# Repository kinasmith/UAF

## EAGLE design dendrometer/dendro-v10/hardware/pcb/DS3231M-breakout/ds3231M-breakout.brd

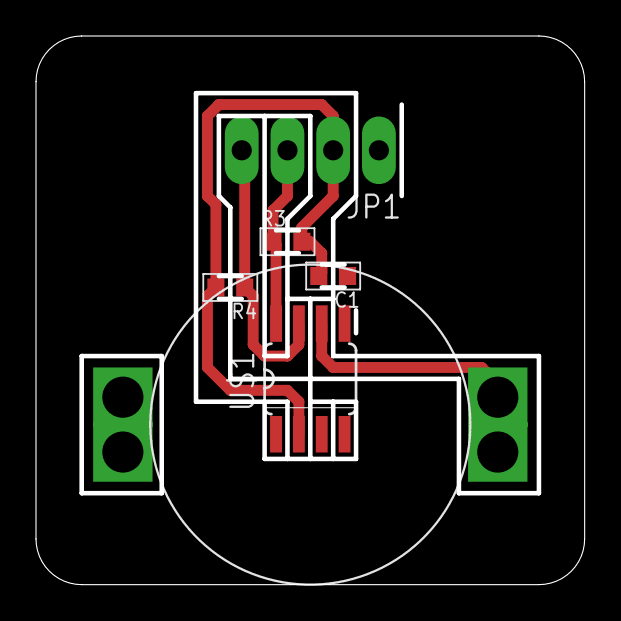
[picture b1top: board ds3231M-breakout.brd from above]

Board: 2 copper layers, 30.5 x 30.5 mm, 6 parts (0 on the bottom side), 5 nets.

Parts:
C1: 0.1uf; C0603-N
JP1: 1X04_LONGPADS
R3, R4: 10k; R0603-N
U$1: DS3231M; SO08
U$2: LINX_2032BAT_HLDER

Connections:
GND: C1.1, JP1.1, U$1.5, U$2.P$1
unnamed: U$1.6, U$2.BAT_POS$1, U$2.BAT_POS$2, U$2.BAT_POS$3, U$2.BAT_POS$4
SCL: JP1.3, R3.1, U$1.8
SDA: JP1.4, R4.1, U$1.7
VCC: C1.2, JP1.2, R3.2, R4.2, U$1.2

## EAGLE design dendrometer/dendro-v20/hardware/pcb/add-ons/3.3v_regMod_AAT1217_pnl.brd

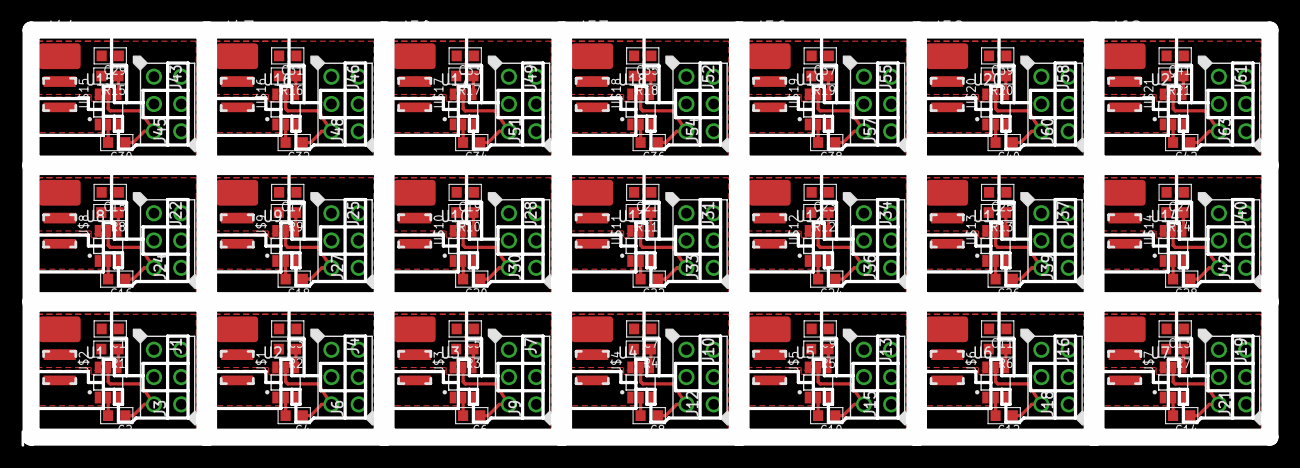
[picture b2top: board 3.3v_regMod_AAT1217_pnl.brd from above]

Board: 2 copper layers, 116.0 x 38.6 mm, 168 parts (0 on the bottom side), 105 nets.

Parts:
C1, C2, C3, C4, C5, C6, C7, C8, C9, C10, C11, C12, C13, C14, C15, C16, C17, C18, C19, C20, C21, C22, C23, C24, C25, C26, C27, C28, C29, C30, C31, C32, C33, C34, C35, C36, C37, C38, C39, C40, C41, C42: C0603-N
J1, J3, J4, J6, J7, J9, J10, J12, J13, J15, J16, J18, J19, J21, J22, J24, J25, J27, J28, J30, J31, J33, J34, J36, J37, J39, J40, J42, J43, J45, J46, J48, J49, J51, J52, J54, J55, J57, J58, J60, J61, J63: MF-CON-2.54mm-01x03; PTH_2.54MM_01X03
J2, J5, J8, J11, J14, J17, J20, J23, J26, J29, J32, J35, J38, J41, J44, J47, J50, J53, J56, J59, J62: CON_01X01LUX; 1X01_LUXEON-PAD
R1, R2, R3, R4, R5, R6, R7, R8, R9, R10, R11, R12, R13, R14, R15, R16, R17, R18, R19, R20, R21: 1M; R0603-N
U1, U2, U3, U4, U5, U6, U7, U8, U9, U10, U11, U12, U13, U14, U15, U16, U17, U18, U19, U20, U21: AAT1217-SOT23-6; SOT23-6
U$1, U$2, U$3, U$4, U$5, U$6, U$7, U$8, U$9, U$10, U$11, U$12, U$13, U$14, U$15, U$16, U$17, U$18, U$19, U$20, U$21: L3030

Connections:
3V1: C4.1, J4.P$3, U2.5
3V2: C6.1, J7.P$3, U3.5
3V3: C2.1, J1.P$3, U1.5
3V4: C8.1, J10.P$3, U4.5
3V5: C10.1, J13.P$3, U5.5
3V6: C12.1, J16.P$3, U6.5
3V7: C14.1, J19.P$3, U7.5
3V8: C16.1, J22.P$3, U8.5
3V9: C18.1, J25.P$3, U9.5
3V10: C20.1, J28.P$3, U10.5
3V11: C22.1, J31.P$3, U11.5
3V12: C24.1, J34.P$3, U12.5
3V13: C26.1, J37.P$3, U13.5
3V14: C28.1, J40.P$3, U14.5
3V15: C30.1, J43.P$3, U15.5
3V16: C32.1, J46.P$3, U16.5
3V17: C34.1, J49.P$3, U17.5
3V18: C36.1, J52.P$3, U18.5
3V19: C38.1, J55.P$3, U19.5
3V20: C40.1, J58.P$3, U20.5
3V21: C42.1, J61.P$3, U21.5
GND: C1.1, C2.2, J1.P$1, U1.2
GND1: C3.1, C4.2, J4.P$1, U2.2
GND2: C5.1, C6.2, J7.P$1, U3.2
GND3: C7.1, C8.2, J10.P$1, U4.2
GND4: C9.1, C10.2, J13.P$1, U5.2
GND5: C11.1, C12.2, J16.P$1, U6.2
GND6: C13.1, C14.2, J19.P$1, U7.2
GND7: C15.1, C16.2, J22.P$1, U8.2
GND8: C17.1, C18.2, J25.P$1, U9.2
GND9: C19.1, C20.2, J28.P$1, U10.2
GND10: C21.1, C22.2, J31.P$1, U11.2
GND11: C23.1, C24.2, J34.P$1, U12.2
GND12: C25.1, C26.2, J37.P$1, U13.2
GND13: C27.1, C28.2, J40.P$1, U14.2
GND14: C29.1, C30.2, J43.P$1, U15.2
GND15: C31.1, C32.2, J46.P$1, U16.2
GND16: C33.1, C34.2, J49.P$1, U17.2
GND17: C35.1, C36.2, J52.P$1, U18.2
GND18: C37.1, C38.2, J55.P$1, U19.2
GND19: C39.1, C40.2, J58.P$1, U20.2
GND20: C41.1, C42.2, J61.P$1, U21.2
unnamed: U1.1, U$2.P$2
unnamed: U2.1, U$1.P$2
unnamed: R1.1, U1.4
unnamed: R2.1, U2.4
unnamed: U3.1, U$3.P$2
unnamed: R3.1, U3.4
unnamed: U4.1, U$4.P$2
unnamed: R4.1, U4.4
unnamed: U5.1, U$5.P$2
unnamed: R5.1, U5.4
unnamed: U6.1, U$6.P$2
unnamed: R6.1, U6.4
unnamed: U7.1, U$7.P$2
unnamed: R7.1, U7.4
unnamed: U8.1, U$8.P$2
unnamed: R8.1, U8.4
unnamed: U9.1, U$9.P$2
unnamed: R9.1, U9.4
unnamed: U10.1, U$10.P$2
unnamed: R10.1, U10.4
unnamed: U11.1, U$11.P$2
unnamed: R11.1, U11.4
unnamed: U12.1, U$12.P$2
unnamed: R12.1, U12.4
unnamed: U13.1, U$13.P$2
unnamed: R13.1, U13.4
unnamed: U14.1, U$14.P$2
unnamed: R14.1, U14.4
unnamed: U15.1, U$15.P$2
unnamed: R15.1, U15.4
unnamed: U16.1, U$16.P$2
unnamed: R16.1, U16.4
unnamed: U17.1, U$17.P$2
unnamed: R17.1, U17.4
unnamed: U18.1, U$18.P$2
unnamed: R18.1, U18.4
unnamed: U19.1, U$19.P$2
unnamed: R19.1, U19.4
unnamed: U20.1, U$20.P$2
unnamed: R20.1, U20.4
unnamed: U21.1, U$21.P$2
unnamed: R21.1, U21.4
V_BAT: C1.2, J2.P$1, R1.2, U1.6, U$2.P$1
V_BAT1: C3.2, J5.P$1, R2.2, U2.6, U$1.P$1
V_BAT2: C5.2, J8.P$1, R3.2, U3.6, U$3.P$1
V_BAT3: C7.2, J11.P$1, R4.2, U4.6, U$4.P$1
V_BAT4: C9.2, J14.P$1, R5.2, U5.6, U$5.P$1
V_BAT5: C11.2, J17.P$1, R6.2, U6.6, U$6.P$1
V_BAT6: C13.2, J20.P$1, R7.2, U7.6, U$7.P$1
V_BAT7: C15.2, J23.P$1, R8.2, U8.6, U$8.P$1
V_BAT8: C17.2, J26.P$1, R9.2, U9.6, U$9.P$1
V_BAT9: C19.2, J29.P$1, R10.2, U10.6, U$10.P$1
V_BAT10: C21.2, J32.P$1, R11.2, U11.6, U$11.P$1
V_BAT11: C23.2, J35.P$1, R12.2, U12.6, U$12.P$1
V_BAT12: C25.2, J38.P$1, R13.2, U13.6, U$13.P$1
V_BAT13: C27.2, J41.P$1, R14.2, U14.6, U$14.P$1
V_BAT14: C29.2, J44.P$1, R15.2, U15.6, U$15.P$1
V_BAT15: C31.2, J47.P$1, R16.2, U16.6, U$16.P$1
V_BAT16: C33.2, J50.P$1, R17.2, U17.6, U$17.P$1
V_BAT17: C35.2, J53.P$1, R18.2, U18.6, U$18.P$1
V_BAT18: C37.2, J56.P$1, R19.2, U19.6, U$19.P$1
V_BAT19: C39.2, J59.P$1, R20.2, U20.6, U$20.P$1
V_BAT20: C41.2, J62.P$1, R21.2, U21.6, U$21.P$1

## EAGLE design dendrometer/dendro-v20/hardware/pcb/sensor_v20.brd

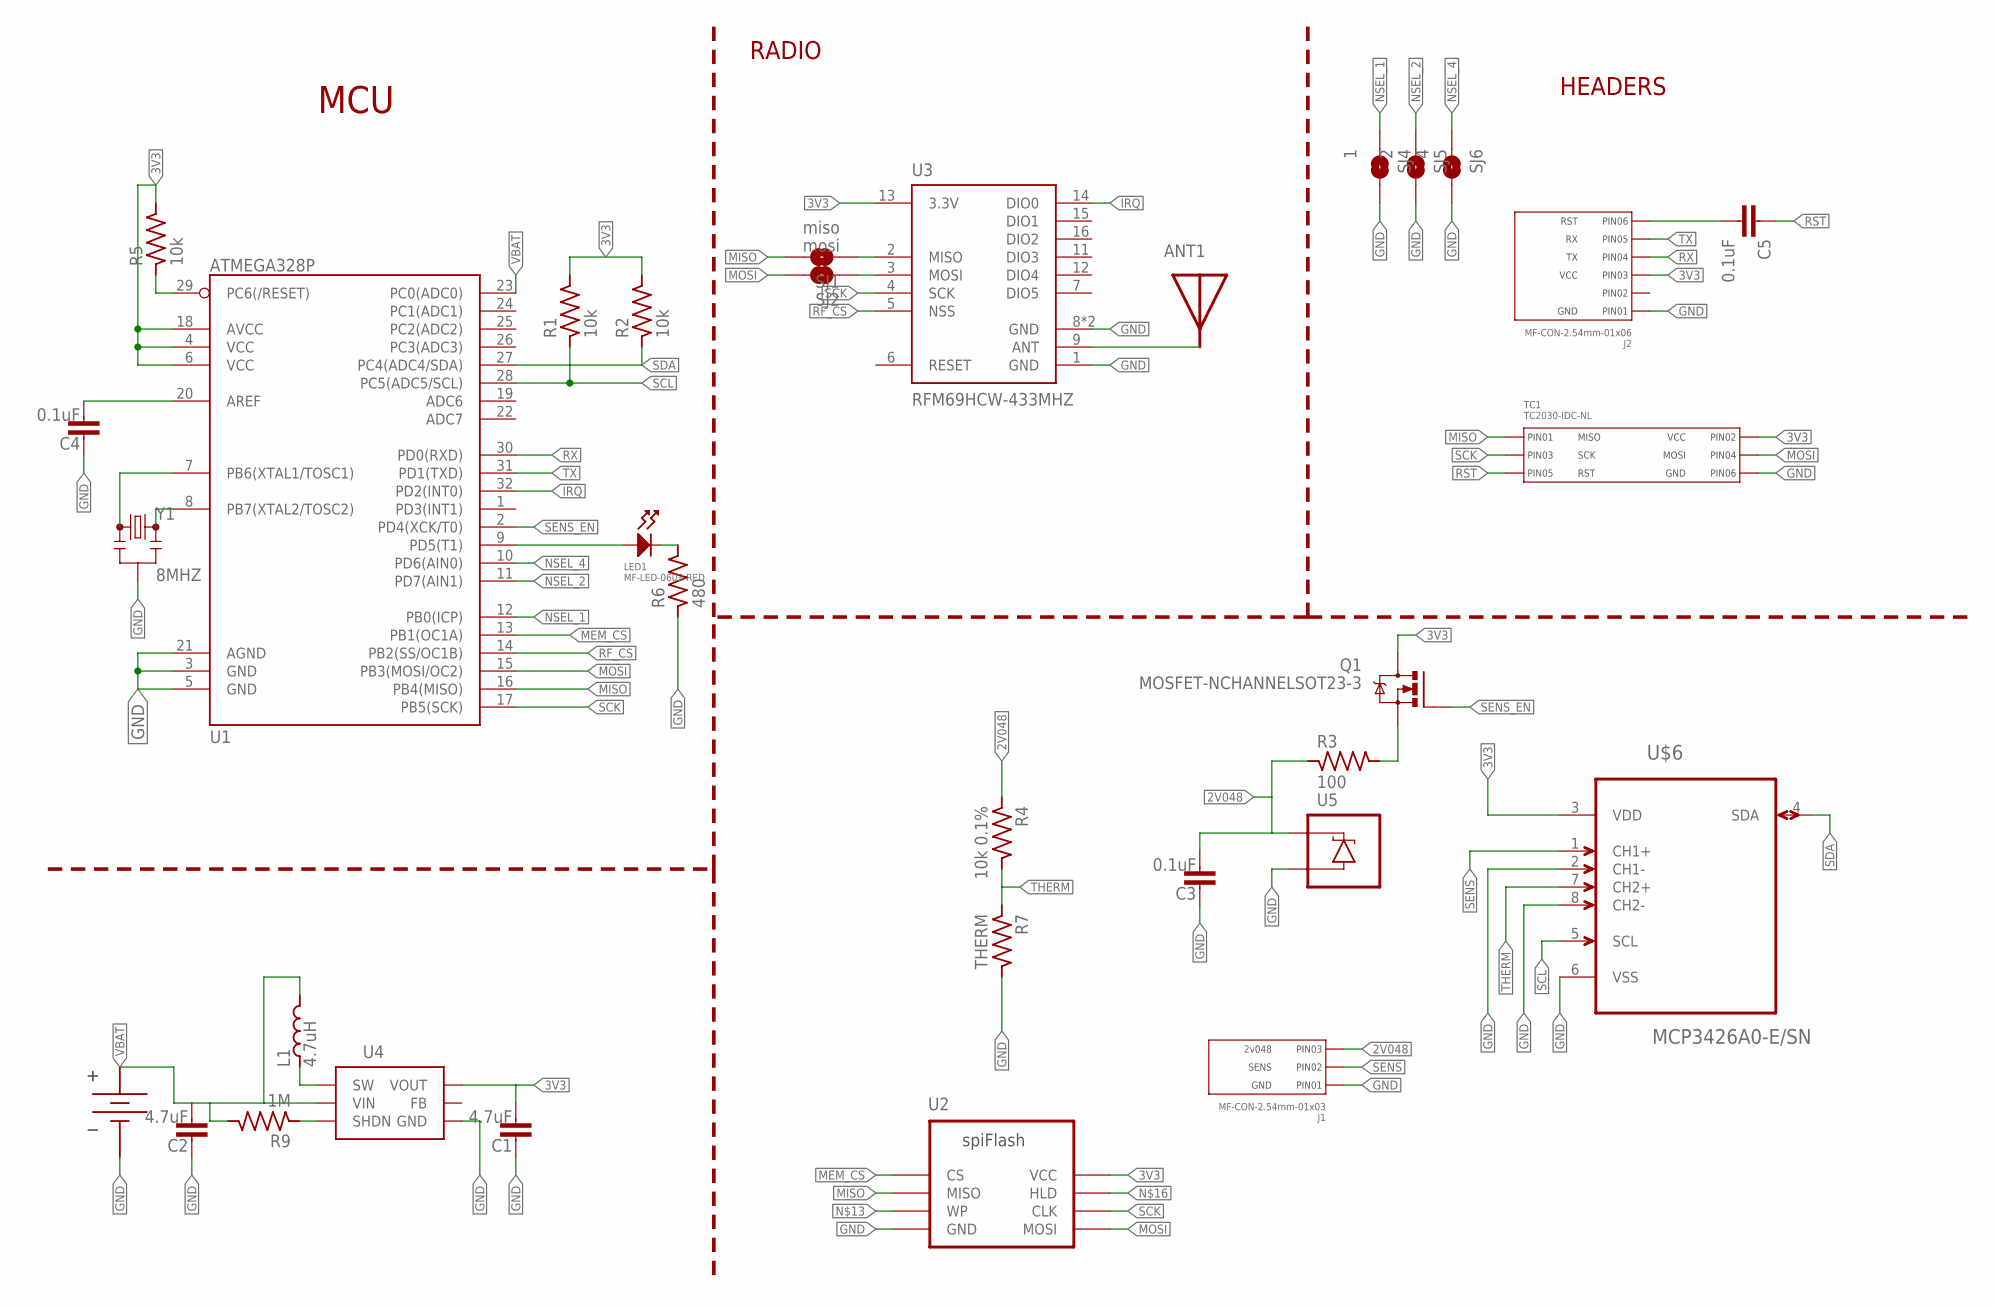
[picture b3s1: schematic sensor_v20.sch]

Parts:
ANT1: ANTENNA-433_CHIP; ANT_433_CHIP
C1, C2: 4.7uF; C0603-N
C3, C4, C5: 0.1uF; C0603-N
J1: MF-CON-2.54mm-01x03; PTH_2.54MM_01X03; PARTNO 0022053031
J2: MF-CON-2.54mm-01x06; PTH_2.54MM_01X06
L1: 4.7uH; L3030
LED1: MF-LED-0603-RED; LED0603
Q1: MOSFET-NCHANNELSOT23-3; SOT23-3
R1, R2, R5: 10k; R0603-N
R3: 100; R0603-N
R4: 10k 0.1%; R0603-N; PARTNO 0.1% !!
R6: 480; R0603-N
R7: THERM; R0603-N; PARTNO FIND PART!!
R9: 1M; R0603-N
SJ1: miso; SJ_2S-NOTRACE
SJ2: mosi; SJ_2S-NOTRACE
SJ4: 1; SJ_2S-NOTRACE
SJ5: 2; SJ_2S-NOTRACE
SJ6: 4; SJ_2S-NOTRACE
TC1: TC2030-IDC-NL
U1: ATMEGA328P; TQFP32
U2: WINBOND_FLASH_4MBIT-SOIC; SOIC8
U3: RFM69HCW-433MHZ; RFM69HCW-XXXS2
U4: AAT1217-SOT23-6; SOT23-6
U5: LM4040-SOT-23-3; SOT23-3
U$1: KEYSTONEAAHOLDER_2CELL
U$6: MCP3426A0-E/SN; SOIC127P600X175-8N
Y1: 8MHZ; RESONATOR-SMD

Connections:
2V048: C3.2, J1.P$3 (PIN3), R3.1, R4.1, U5.1 (C)
3V3: C1.2, J2.P$3 (PIN3), Q1.3 (D), R1.2, R2.2, R5.2, TC1.P$2 (PIN2), U1.4 (VCC), U1.6 (VCC), U1.18 (AVCC), U2.8 (VCC), U3.13 (3.3V), U4.5 (VOUT), U$6.3 (VDD)
GND: C1.1, C2.1, C3.1, C4.1, J1.P$1 (PIN1), J2.P$1 (PIN1), R6.1, R7.2, SJ4.2, SJ5.2, SJ6.2, TC1.P$6 (PIN6), U1.3 (GND), U1.5 (GND), U1.21 (AGND), U2.4 (GND), U3.1 (GND), U3.8 (GND), U3.10 (GND), U4.2 (GND), U5.2 (A), U$1.P$2 (GND), U$6.2 (CH1-), U$6.6 (VSS), U$6.8 (CH2-), Y1.2
IRQ: U1.32 (PD2(INT0)), U3.14 (DIO0)
MEM_CS: U1.13 (PB1(OC1A)), U2.1 (CS)
MISO: SJ1.2, TC1.P$1 (PIN1), U1.16 (PB4(MISO)), U2.2 (MISO)
MOSI: SJ2.2, TC1.P$4 (PIN4), U1.15 (PB3(MOSI/OC2)), U2.5 (MOSI)
unnamed: R9.1, U4.4 (SHDN)
unnamed: ANT1.1, U3.9 (ANT)
unnamed: LED1.ANODE, U1.9 (PD5(T1))
unnamed: C4.2, U1.20 (AREF)
unnamed: LED1.CATHODE, R6.2
unnamed: L1.P$1, U4.1 (SW)
unnamed: U1.7 (PB6(XTAL1/TOSC1)), Y1.1
unnamed: U1.8 (PB7(XTAL2/TOSC2)), Y1.3
unnamed: SJ1.1, U3.2 (MISO)
unnamed: C5.2, J2.P$6 (PIN6)
unnamed: SJ2.1, U3.3 (MOSI)
unnamed: Q1.2 (S), R3.2
NSEL_1: SJ4.1, U1.12 (PB0(ICP))
NSEL_2: SJ5.1, U1.11 (PD7(AIN1))
NSEL_4: SJ6.1, U1.10 (PD6(AIN0))
RF_CS: U1.14 (PB2(SS/OC1B)), U3.5 (NSS)
RST: C5.1, R5.1, TC1.P$5 (PIN5), U1.29 (PC6(/RESET))
RX: J2.P$4 (PIN4), U1.30 (PD0(RXD))
SCK: TC1.P$3 (PIN3), U1.17 (PB5(SCK)), U2.6 (CLK), U3.4 (SCK)
SCL: R1.1, U1.28 (PC5(ADC5/SCL)), U$6.5 (SCL)
SDA: R2.1, U1.27 (PC4(ADC4/SDA)), U$6.4 (SDA)
SENS: J1.P$2 (PIN2), U$6.1 (CH1+)
SENS_EN: Q1.1 (G), U1.2 (PD4(XCK/T0))
THERM: R4.2, R7.1, U$6.7 (CH2+)
TX: J2.P$5 (PIN5), U1.31 (PD1(TXD))
VBAT: C2.2, L1.P$2, R9.2, U1.23 (PC0(ADC0)), U4.6 (VIN), U$1.P$1 (VBAT)

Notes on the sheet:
MCU
RADIO
HEADERS

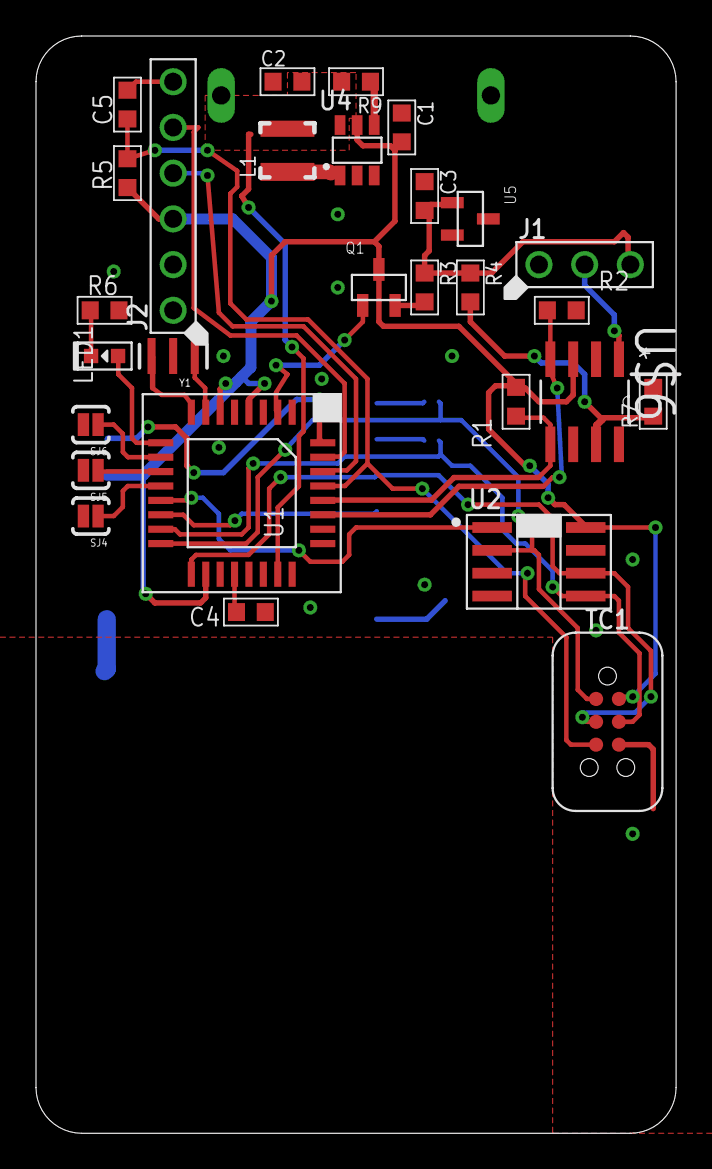
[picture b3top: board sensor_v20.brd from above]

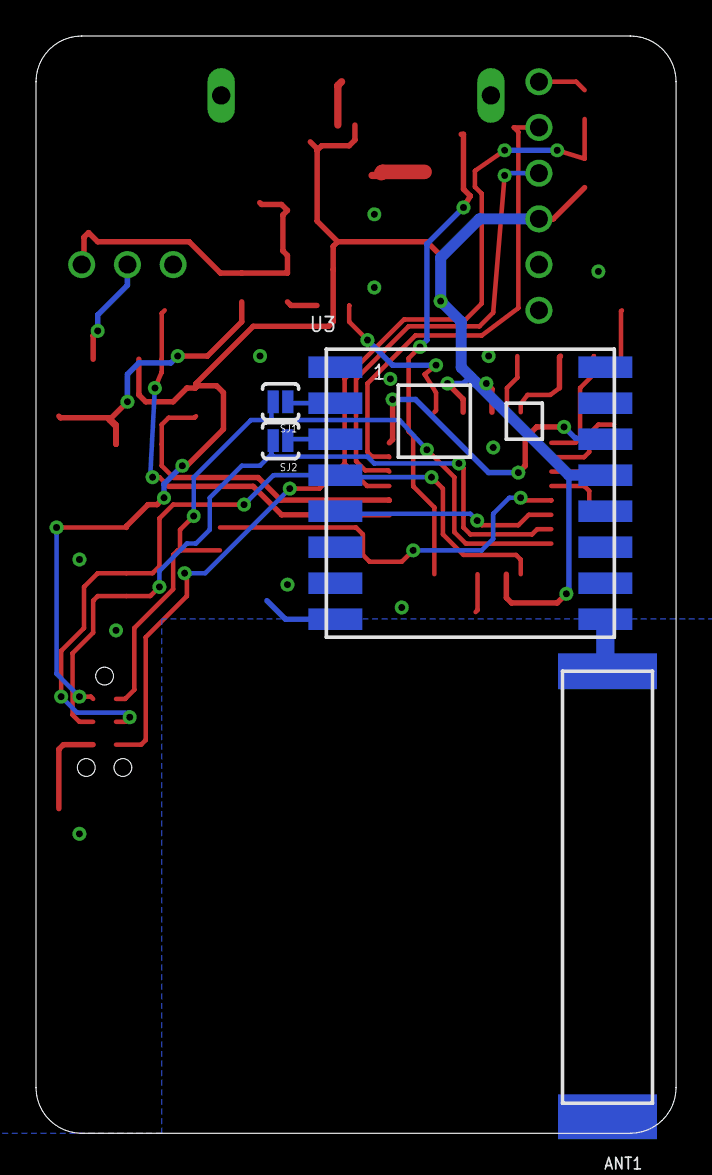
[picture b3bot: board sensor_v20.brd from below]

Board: 2 copper layers, 35.6 x 61.0 mm, 33 parts (4 on the bottom side), 33 nets.

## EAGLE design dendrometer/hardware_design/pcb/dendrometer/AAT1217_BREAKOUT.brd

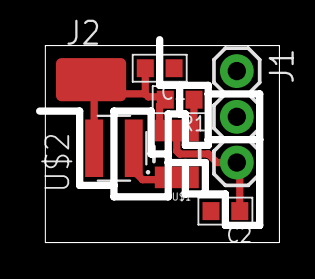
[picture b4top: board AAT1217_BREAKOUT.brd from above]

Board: 2 copper layers, 13.0 x 10.9 mm, 7 parts (0 on the bottom side), 5 nets.

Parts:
C1, C2: C0603-N
J1: 1X03
J2: LUXEON-PAD
R1: R0603-N
U$1: AAT1217; SOT23-6
U$2: INDUCTORS_WURTH; WURTH_10UH_650MA

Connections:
GND: C1.1, C2.2, J1.1, U$1.2
unnamed: R1.1, U$1.4
unnamed: C1.2, J2.P$1, R1.2, U$1.6, U$2.P$2
unnamed: U$1.1, U$2.P$1
VOUT: C2.1, J1.3, U$1.5

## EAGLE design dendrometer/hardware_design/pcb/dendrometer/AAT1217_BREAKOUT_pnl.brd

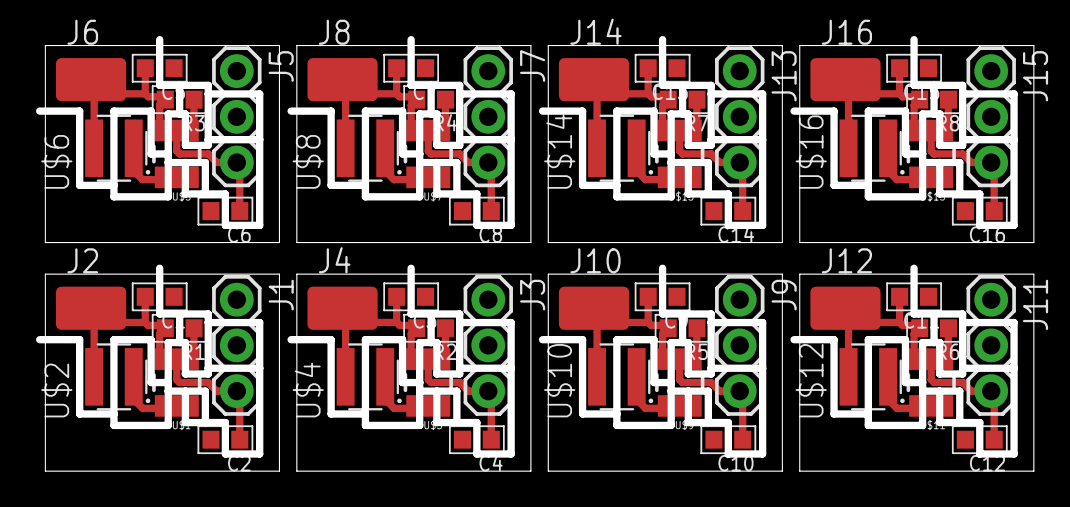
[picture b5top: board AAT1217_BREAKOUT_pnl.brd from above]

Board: 2 copper layers, 55.2 x 24.0 mm, 56 parts (0 on the bottom side), 40 nets.

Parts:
C1, C2, C3, C4, C5, C6, C7, C8, C9, C10, C11, C12, C13, C14, C15, C16: C0603-N
J1, J3, J5, J7, J9, J11, J13, J15: 1X03
J2, J4, J6, J8, J10, J12, J14, J16: LUXEON-PAD
R1, R2, R3, R4, R5, R6, R7, R8: R0603-N
U$1, U$3, U$5, U$7, U$9, U$11, U$13, U$15: AAT1217; SOT23-6
U$2, U$4, U$6, U$8, U$10, U$12, U$14, U$16: INDUCTORS_WURTH; WURTH_10UH_650MA

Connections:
GND: C1.1, C2.2, J1.1, U$1.2
GND1: C3.1, C4.2, J3.1, U$3.2
GND2: C5.1, C6.2, J5.1, U$5.2
GND3: C7.1, C8.2, J7.1, U$7.2
GND4: C9.1, C10.2, J9.1, U$9.2
GND5: C11.1, C12.2, J11.1, U$11.2
GND6: C13.1, C14.2, J13.1, U$13.2
GND7: C15.1, C16.2, J15.1, U$15.2
unnamed: R1.1, U$1.4
unnamed: C1.2, J2.P$1, R1.2, U$1.6, U$2.P$2
unnamed: R2.1, U$3.4
unnamed: U$1.1, U$2.P$1
unnamed: C3.2, J4.P$1, R2.2, U$3.6, U$4.P$2
unnamed: U$3.1, U$4.P$1
unnamed: R3.1, U$5.4
unnamed: C5.2, J6.P$1, R3.2, U$5.6, U$6.P$2
unnamed: U$5.1, U$6.P$1
unnamed: R4.1, U$7.4
unnamed: C7.2, J8.P$1, R4.2, U$7.6, U$8.P$2
unnamed: U$7.1, U$8.P$1
unnamed: R5.1, U$9.4
unnamed: C9.2, J10.P$1, R5.2, U$9.6, U$10.P$2
unnamed: U$9.1, U$10.P$1
unnamed: R6.1, U$11.4
unnamed: C11.2, J12.P$1, R6.2, U$11.6, U$12.P$2
unnamed: U$11.1, U$12.P$1
unnamed: R7.1, U$13.4
unnamed: C13.2, J14.P$1, R7.2, U$13.6, U$14.P$2
unnamed: U$13.1, U$14.P$1
unnamed: R8.1, U$15.4
unnamed: C15.2, J16.P$1, R8.2, U$15.6, U$16.P$2
unnamed: U$15.1, U$16.P$1
VOUT: C2.1, J1.3, U$1.5
VOUT1: C4.1, J3.3, U$3.5
VOUT2: C6.1, J5.3, U$5.5
VOUT3: C8.1, J7.3, U$7.5
VOUT4: C10.1, J9.3, U$9.5
VOUT5: C12.1, J11.3, U$11.5
VOUT6: C14.1, J13.3, U$13.5
VOUT7: C16.1, J15.3, U$15.5

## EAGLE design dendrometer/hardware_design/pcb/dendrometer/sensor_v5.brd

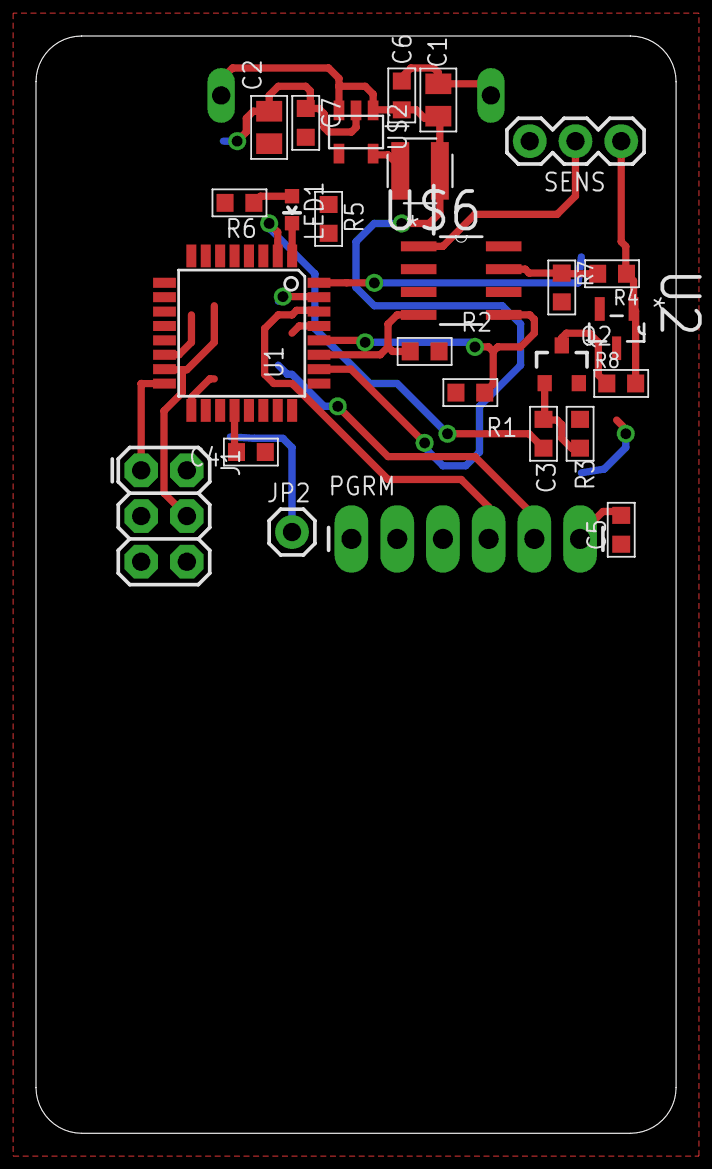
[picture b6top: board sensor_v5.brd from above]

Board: 2 copper layers, 35.6 x 61.0 mm, 28 parts (1 on the bottom side), 25 nets.

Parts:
C1, C2: 10uF; C0805-N
C3, C4, C5, C6, C7: 0.1uF; C0603-N
J1: AVR_SPI_PRG_6PTH; 2X3
JP2: M01PTH; 1X01
LED1: LED-0603
PGRM: 1X06_LONGPADS
Q2: MOSFET-P; SOT23-3
R1, R2, R4, R5: 10k; R0603-N
R3: 1M; R0603-N
R6: 480; R0603-N
R7: THERM; R0603-N
R8: 330; R0603-N
SENS: 1X03
U1: ATMEGA328P; TQFP32-08
U2: LM4040A20IDBZT; SOT95P237X112-3N
U$1: KEYSTONEAAHOLDER_2CELL
U$2: TPS61097-33; SOT23-5
U$4: 4.7uH; WURTH_10UH_650MA
U$5: RFM69; RFM69W-MINPADS
U$6: MCP3426A0-E/SN; SOIC127P600X175-8N

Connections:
G: C3.1, Q2.1, R3.1
GND: C1.2, C2.2, C4.1, C6.2, C7.2, J1.6, PGRM.1, R7.2, SENS.1, U1.3, U1.5, U1.21, U2.2, U$1.P$2, U$2.P$2, U$5.GND, U$6.2, U$6.6, U$6.8
IRQ: U1.32, U$5.DIO0
MISO: J1.1, U1.16, U$5.MISO
MOSI: J1.4, U1.15, U$5.MOSI
unnamed: U$2.P$5, U$4.P$1
unnamed: C4.2, U1.20
unnamed: LED1.C, U1.1
unnamed: JP2.1, U$5.ANA
unnamed: LED1.A, R6.2
unnamed: C5.2, PGRM.6
RST: C5.1, J1.5, R5.1, U1.29
RX: PGRM.4, U1.30
SCK: J1.3, U1.17, U$5.SCK
SCL: R1.1, U1.28, U$6.5
SDA: R2.1, U1.27, U$6.4
SENS: SENS.2, U$6.1
SENS_EN: C3.2, U1.2
SS: U1.14, U$5.NSS
S_EN: Q2.3, R8.1
THERM: R4.2, R7.1, U$6.7
TX: PGRM.5, U1.31
V3.3: C2.1, C7.1, J1.2, Q2.2, R1.2, R2.2, R3.2, R5.2, R6.1, U1.4, U1.6, U1.18, U$2.P$4, U$5.VDD, U$6.3
VBAT: C1.1, C6.1, U1.26, U$1.P$1, U$2.P$1, U$2.P$3, U$4.P$2
V_REF: R4.1, R8.2, SENS.3, U2.1

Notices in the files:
parts and their libraries:
SparkFun-Connectors: Licensing: CC v3.0 Share-Alike You are welcome to use this library for commercial purposes.
SparkFun-Aesthetics: Licensing: Creative Commons ShareAlike 4.0 International - https://creativecommons.org/licenses/by-sa/4.0
